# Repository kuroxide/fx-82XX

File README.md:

This project contains designs for converting a Casio fx-8200 AU (or similar ClassWiz model calculators) into a general purpose computer by putting a Raspberry Pi Zero inside.

## Rationale
There is no rationale, in fact, this project is very irrationale (just buy a phone) \
The only reason to make this is to troll NESA.

## Design Process
Things are big. Although the Pi Zero is tiny, the space inside the calculator is yet tinier. \
Unmodified, there is only about 3mm of vertical clearance to fit stuff inside the case of the calculator, and it is divided up by reinforcing ribs. The Pi Zero by itself takes up about 1/3 of the usable area inside the calculator.

Thus, we arrive at the winning formula: *Dremel everything.* \
To increase the amount of space available, the ribs are cut out with a dremel tool (you could also use a file if you are very, very dedicated). A custom PCB is used for the keypad; the membrane is re-used since custom making them is a pain in the \[REDACTED] \
The overall design can be split up into 4 parts:
- The keypad
- The power supply
- The display
- The computer itself

### The Keypad
Since the keys and membrane are re-used from the calculator, the only issue is making a custom PCB with a keyboard matrix on it. Vertical clearance is limited, a PCB thickness of 1mm or less is *necessary* to allow everything else to fit. The distances between the keys were measured with a set of calipers and a very good sense of eyeballing, to produce the final matrix layout. \
The Pi's GPIO pins are very useful, especially because there are enough of them to run both a keyboard matrix as well as the display over SPI. The row and column traces on the keypad are directly soldered to the Pi as a HAT (although in this case it's attached on the bottom, so it would be a HAB).

### The Power Supply
BATTERIES. The Pi Zero (and most other SBCs for that matter) run on 5V power, but the AAA cell used by the calculator can provide at maximum around 1.8V. Lithium cells run at 3.7V, which is *allegedly* able to power the Pi, but is definitely not within spec. Therefore, a boost converter has to be used, which solves the voltage issue. \
A Raspberry Pi Zero 2W averages around 160mAh when idle. Although the main usage (running a calculator or CAS app) is quite light, it also has to power the display, as well as potentially run other programs. Due to the laws of physics, a AAA cell connected to a boost converter is ruled out as an option. Instead, a lithium cell is used. \
Commercially available rectangular LiPo cells are usually 7-10mm thick, which is too obese to fit. However, a 10440 cell is about the same size as a AAA, and can fit in the battery terminals of the calculator (never do this on anything that normally runs off AAAs, by the way). The battery terminals are re-used from the calculator, desoldered and then connected to the 5V boost converter. \
Most 10440 cells can provide somewhere in the neighbourhood of 350mAh. At 3.7V, that works out to 1.295Wh. Assuming that 80% of the capacity is usable, there is about 1Wh available to run the Pi. If the Pi is drawing 250mA@5V (because you're trying to calculate 999999999 factorial or something), the Pi can run for a maximum of 1Wh/1.25W = 0.8 hours. You will want to have more than one calculator if you actually want to use this in an exam (which you shouldn't do, because it's pretty stupid). \
More realistically (sort of), assuming 90% of the capacity is usable and the Pi is drawing 200mA, it can run for 1.1655Wh/1W = 1.1655 hours. If you can find a 10440 cell that *actually* provides more than 350mAh reliably, it will be able to run for longer (obviously). Good luck with that though.

### The Display
There are two options:
1. Reverse engineer the display already in the calculator. This is not a good idea, as will quickly be explained.
2. Replace it with a different one.

Why not option 1? The display is connected to the calculator via a ribbon cable that is glued down and possibly also soldered. It is almost impossible to remove it without damaging it. Also, the pinout is unknown, and reverse-engineering it probably isn't worth the effort. \
Option 2 is relatively much easier, but still quite annoying. Most LCD modules are either too large or too small, don't have the right colour, etc.. The closest thing to a suitable display is a 2.66" e-ink display (covered with some green cellophane to give it the right colour). The display can be purchased either by itself and connected to a driver board, or as a display module with a driver chip already attached.

### The Computer Itself
This project is based on a Raspberry Pi Zero W/2/2W, because it is small and relatively powerful, and can have wireless capability. However, it can be easily modified to use most small SBCs. As long as the SBC used can be powered directly from 5V, is under 3mm thick, has SPI pins, and at least 14 GPIOs, it can theoretically be used. Some boards can be made thin enough by desoldering any USB or other ports. The choice of SBC used is a compromise between size, power draw and performance (and to a lesser extent features and support).
Recommendations:
- RPi Zero 2 W for maximum performance, but also maximum power draw
- RPi Zero W / Zero for less performance and less power draw
- Tiny RISC-V boards, for compactness and less power draw but worse support and performance, and no wireless
- Other RPi Zero form factor boards, if they are actually available in your area

## Assembly
Bill of Materials (excl. shipping)
| Part | Cost (AUD) |
| ---- | ---------- |
| Raspberry Pi Zero 2 W | $29.95 |
| Pololu U1V10F5 | $10.05 |
| P-channel MOSFET | $5 for a pack of 10 |
| Keypad PCB | $20 (depends on the fab house) |
| 2.66" Display Module | $25 |
| 10440 Lithium Battery | ~$20 for a pack of 4 |
| Wires | not much |

# Licensing
Code portions of this project are licensed under GPLv3. (See LICENSE) \
This project uses symbols and footprints from the [KiCad libraries](https://www.kicad.org/libraries/) \
Hardware designs in this project are licensed under CC BY-NC-SA 4.0. To view a copy of this license, visit http://creativecommons.org/licenses/by-nc-sa/4.0/

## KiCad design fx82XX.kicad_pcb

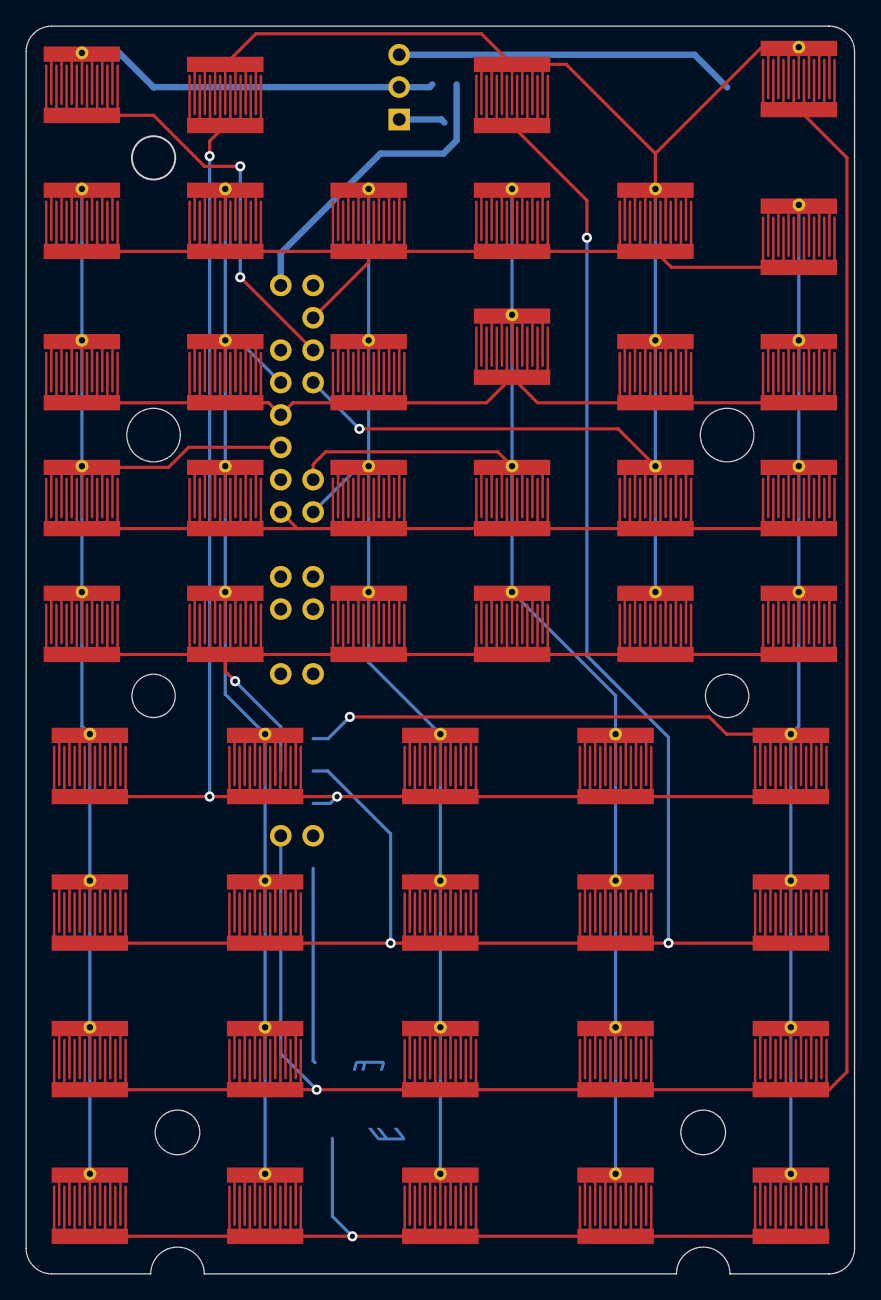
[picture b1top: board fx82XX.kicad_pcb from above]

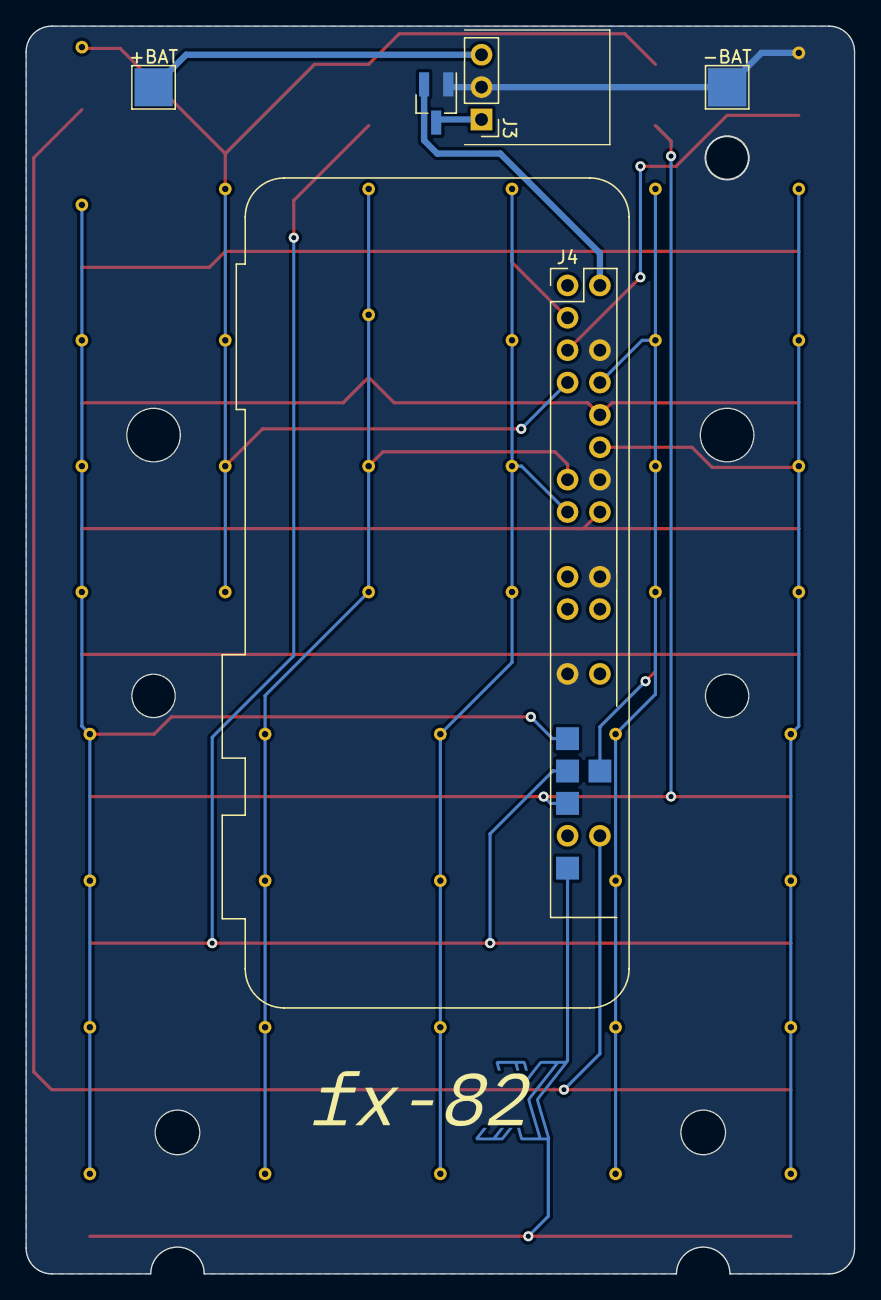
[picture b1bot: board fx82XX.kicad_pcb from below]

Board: 2 copper layers, 65.0 x 97.8 mm, 53 parts (4 on the bottom side), 19 nets.

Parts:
+BAT: VBAT; TestPoint_Pad_3.0x3.0mm
-BAT: GND; TestPoint_Pad_3.0x3.0mm
J3: U1V10F5; PinHeader_1x03_P2.54mm_Vertical
J4: Raspberry_Pi_2_3; Raspberry_Pi_Zero_Socketed_THT_FaceDown_MountingHoles
P1: On; RubberDome_Switch
Q1: MMFTP3401; SOT-23_Handsoldering
SW1, SW2, SW3, SW4, SW5, SW6, SW7, SW8, SW9, SW10, SW11, SW12, SW13, SW14, SW15, SW16, SW17, SW18, SW19, SW20, SW21, SW22, SW23, SW24, SW25, SW26, SW27, SW28, SW29, SW30, SW31, SW32, SW33, SW34, SW35, SW36, SW37, SW38, SW39, SW40, SW41, SW42, SW43, SW44: SW_Push; RubberDome_Switch
SW45: Home; RubberDome_Switch_NoHole
SW46: Up; RubberDome_Switch_NoHole
SW47: Prev; RubberDome_Switch

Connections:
+5V: J4.2 (5V), Q1.2 (S)
+BATT: +BAT.1, J3.3
BOOT: J4.5 (SCL/GPIO3), P1.2
C1: J4.12 (GPIO18/PWM0), SW1.1, SW7.1, SW13.1, SW19.1, SW25.1, SW30.1, SW35.1, SW40.1
C2: J4.8 (GPIO14/TXD), SW2.1, SW8.1, SW14.1, SW20.1, SW26.1, SW31.1, SW36.1, SW41.1
C3: J4.15 (GPIO22), SW3.1, SW9.1, SW15.1, SW21.1, SW27.1, SW32.1, SW37.1, SW42.1
C4: J4.13 (GPIO27), SW4.1, SW10.1, SW16.1, SW22.1, SW28.1, SW33.1, SW38.1, SW43.1
C5: J4.7 (GCLK0/GPIO4), SW5.1, SW11.1, SW17.1, SW23.1, SW45.1, SW46.1, SW47.1
C6: J4.29 (GCLK1/GPIO5), SW6.1, SW12.1, SW18.1, SW24.1, SW29.1, SW34.1, SW39.1, SW44.1
GNDPWR: -BAT.1, J3.2, J4.6 (GND), J4.14 (GND), J4.20 (GND), J4.25 (GND), P1.1, Q1.1 (G)
unnamed: J3.1, Q1.3 (D)
R1: J4.3 (SDA/GPIO2), SW1.2, SW2.2, SW3.2, SW4.2, SW5.2, SW6.2
R2: J4.10 (GPIO15/RXD), SW7.2, SW8.2, SW9.2, SW10.2, SW11.2, SW12.2
R3: J4.16 (GPIO23), SW13.2, SW14.2, SW15.2, SW16.2, SW17.2, SW18.2
R4: J4.32 (PWM0/GPIO12), SW19.2, SW20.2, SW21.2, SW22.2, SW23.2, SW24.2
R5: J4.33 (PWM1/GPIO13), SW25.2, SW26.2, SW27.2, SW28.2, SW29.2, SW45.2
R6: J4.31 (GCLK2/GPIO6), SW30.2, SW31.2, SW32.2, SW33.2, SW34.2, SW46.2
R7: J4.36 (GPIO16), SW35.2, SW36.2, SW37.2, SW38.2, SW39.2, SW47.2
R8: J4.37 (GPIO26), SW40.2, SW41.2, SW42.2, SW43.2, SW44.2

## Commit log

2024-02-20 Add KiCad project files
2024-02-20 Add footprint library
2024-02-20 Add README.md
2024-02-20 Change title to current working name
2024-02-20 I can't spell
2024-02-20 Change symbol references
2024-02-21 Slightly change membrane contact geometry
2024-02-21 Re-route using 2 layers
2024-02-24 Add fx-82XX logo
2024-02-24 Add holes for screws and rivets
2024-03-04 Remove soldermask conflict in logo
2024-03-04 Redesign PCB to be more accurate and better
2024-03-04 Increase size of switch pads for V2
2024-03-30 Kicad 8.0 moment
2024-03-30 Add sym-lib-table
